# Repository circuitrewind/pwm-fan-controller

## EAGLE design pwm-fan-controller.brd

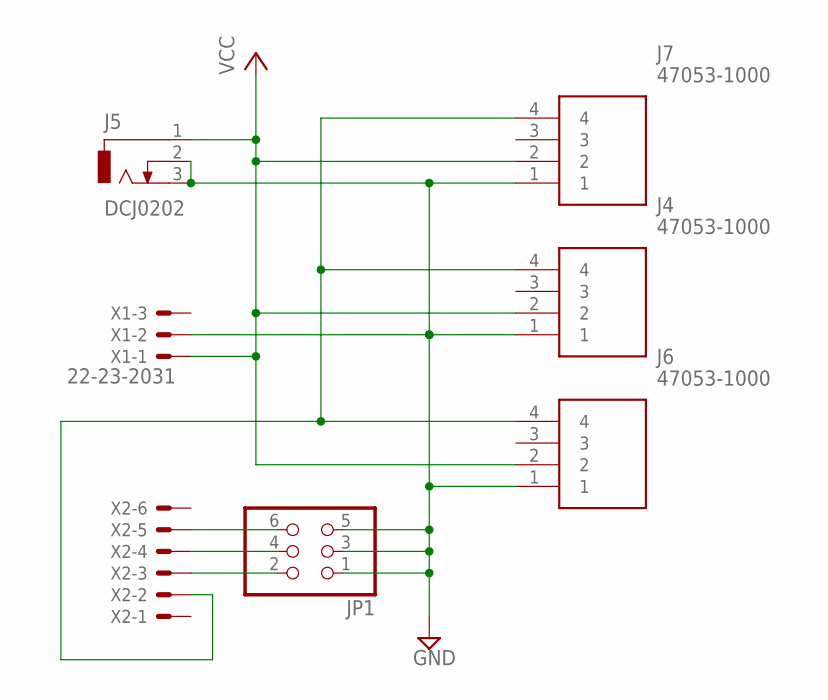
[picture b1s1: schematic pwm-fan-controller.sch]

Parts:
J4, J6, J7: 47053-1000; 470531000
J5: DCJ0202
JP1: PINHD-2X3; 2X03
X1: 22-23-2031
X2: 22-23-2061

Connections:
GND: J4.1, J5.2, J5.3, J6.1, J7.1, JP1.1, JP1.3, JP1.5, X1.2
unnamed: J4.4, J6.4, J7.4, X2.2
unnamed: JP1.6, X2.5
unnamed: JP1.4, X2.4
unnamed: JP1.2, X2.3
VCC: J4.2, J5.1, J6.2, J7.2, X1.1

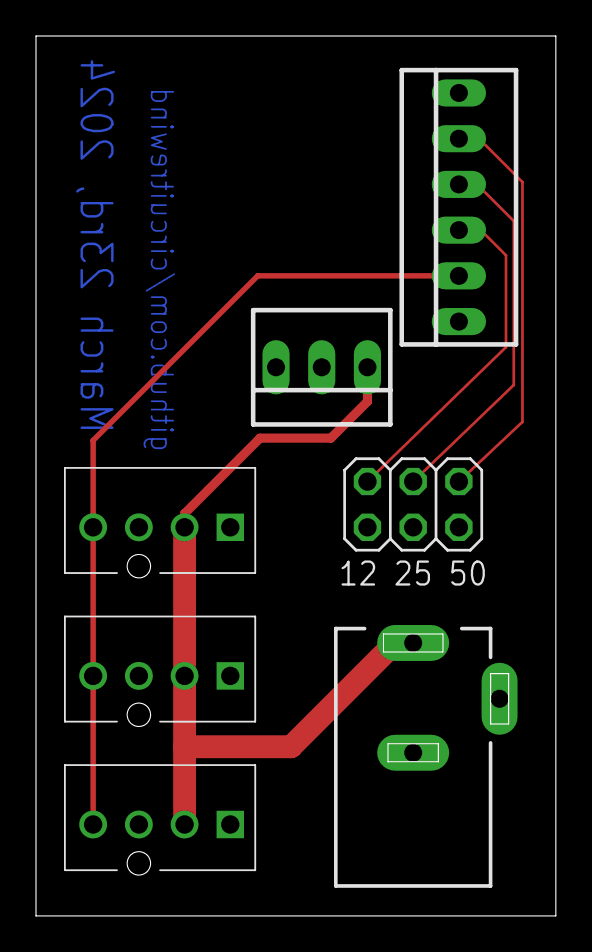
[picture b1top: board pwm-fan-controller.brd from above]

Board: 2 copper layers, 28.9 x 48.9 mm, 7 parts (0 on the bottom side), 6 nets.

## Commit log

2024-04-21 Adding Arduino code
2024-04-21 Adding Eagle board files
